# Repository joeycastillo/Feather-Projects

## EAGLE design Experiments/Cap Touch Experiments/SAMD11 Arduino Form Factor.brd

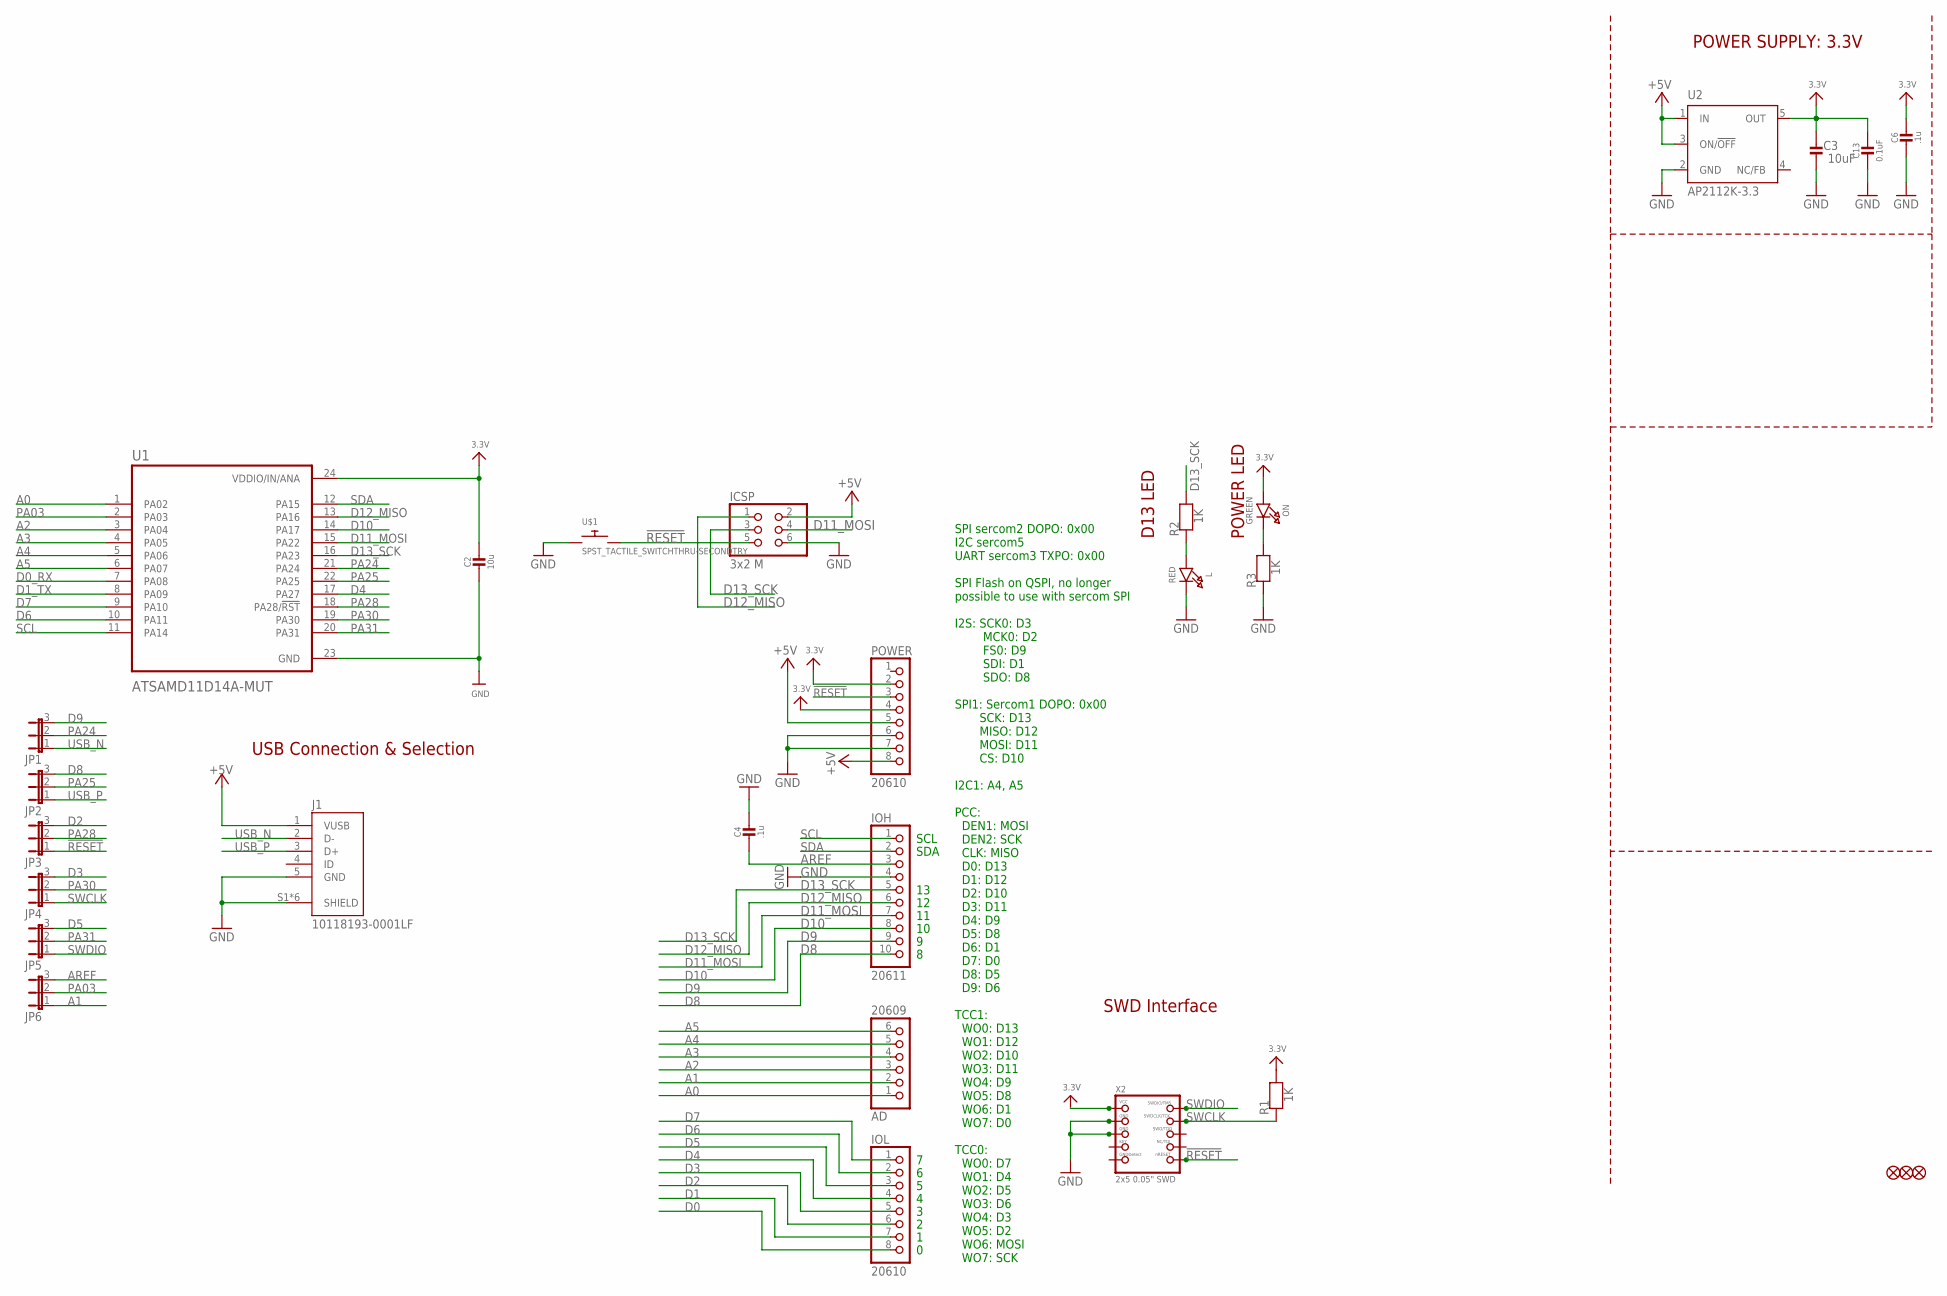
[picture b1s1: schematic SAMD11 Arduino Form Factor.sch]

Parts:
AD: 20609; 1X06_OVALWAVE
C2: 10u; 0805-NO
C3: 10uF; 0805-NO
C4, C6: .1u; 0805-NO
C13: 0.1uF; 0805-NO
FD1, FD2, FD3: FIDUCIAL_1MM
ICSP: 3x2 M; 2X03_ROUND_70MIL
IOH: 20611; 1X10_OVALWAVE
IOL: 20610; 1X08_OVALWAVE
J1: 10118193-0001LF; FCI_10118193-0001LF
JP1, JP2, JP3, JP4, JP5, JP6: JP2E; JP2
L: RED; CHIPLED_0805_NOOUTLINE
ON: GREEN; CHIPLED_0805_NOOUTLINE
POWER: 20610; 1X08_OVALWAVE
R1, R2, R3: 1K; 0805-NO
U1: ATSAMD11D14A-MUT; QFN50P400X400X90-25N
U2: AP2112K-3.3; SOT23-DBV
U$1: SPST_TACTILE_SWITCHTHRU-SECONDTRY; MJTP1250-TRY2
X2: 2x5 0.05" SWD; 2X05_1.27MM_BOX_POSTS

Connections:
3.3V: C2.2, C3.2, C6.2, C13.1, ON.A, POWER.2, POWER.4, R1.2, U1.24 (VDDIO/IN/ANA), U2.5 (OUT), X2.1 (VCC)
!RESET: ICSP.5, JP3.1, POWER.3, U$1.P$2, X2.10 (NRESET)
+5V: ICSP.2, POWER.5, POWER.8, U2.1 (IN), U2.3 (ON/!OFF)
A0: AD.1, U1.1 (PA02)
A1: AD.2, JP6.1
A2: AD.3, U1.3 (PA04)
A3: AD.4, U1.4 (PA05)
A4: AD.5, U1.5 (PA06)
A5: AD.6, U1.6 (PA07)
AREF: C4.1, IOH.3, JP6.3
D0: IOL.8
D0_RX: U1.7 (PA08)
D1: IOL.7
D1_TX: U1.8 (PA09)
D2: IOL.6, JP3.3
D3: IOL.5, JP4.3
D4: IOL.4, U1.17 (PA27)
D5: IOL.3, JP5.3
D6: IOL.2, U1.10 (PA11)
D7: IOL.1, U1.9 (PA10)
D8: IOH.10, JP2.3
D9: IOH.9, JP1.3
D10: IOH.8, U1.14 (PA17)
D11_MOSI: ICSP.4, IOH.7, U1.15 (PA22)
D12_MISO: ICSP.1, IOH.6, U1.13 (PA16)
D13_SCK: ICSP.3, IOH.5, R2.2, U1.16 (PA23)
GND: C2.1, C3.1, C4.2, C6.1, C13.2, ICSP.6, IOH.4, J1.5 (GND), J1.S1 (SHIELD), J1.S2 (SHIELD), J1.S3 (SHIELD), J1.S4 (SHIELD), J1.S5 (SHIELD), J1.S6 (SHIELD), L.C, POWER.6, POWER.7, R3.1, U1.23 (GND), U2.2 (GND), U$1.P$1, X2.3 (GND), X2.5 (GND)
unnamed: L.A, R2.1
unnamed: ON.C, R3.2
PA03: JP6.2, U1.2 (PA03)
PA24: JP1.2, U1.21 (PA24)
PA25: JP2.2, U1.22 (PA25)
PA28: JP3.2, U1.18 (PA28/!RST)
PA30: JP4.2, U1.19 (PA30)
PA31: JP5.2, U1.20 (PA31)
SCL: IOH.1, U1.11 (PA14)
SDA: IOH.2, U1.12 (PA15)
SWCLK: JP4.1, R1.1, X2.4 (SWDCLK)
SWDIO: JP5.1, X2.2 (SWDIO)
USB_N: J1.2 (D-), JP1.1
USB_P: J1.3 (D+), JP2.1

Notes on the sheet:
SDA
SCL
USB Connection & Selection
POWER SUPPLY: 3.3V
POWER LED
D13 LED
SWD Interface
SPI sercom2 DOPO: 0x00 I2C sercom5 UART sercom3 TXPO: 0x00 SPI Flash on QSPI, no longer possible to use with sercom SPI I2S: SCK0: D3 MCK0: D2 FS0: D9 SDI: D1 SDO: D8 SPI1: Sercom1 DOPO: 0x00 SCK: D13 MISO: D12 MOSI: D11 CS: D10 I2C1: A4, A5 PCC: DEN1: MOSI DEN2: SCK CLK: MISO D0: D13 D1: D12 D2: D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

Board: 2 copper layers, 31 parts (1 on the bottom side), 37 nets, no tracks yet.

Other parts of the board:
U$23: METROM4_REVF_TOP
U$27: METROM4_REVF_BOT

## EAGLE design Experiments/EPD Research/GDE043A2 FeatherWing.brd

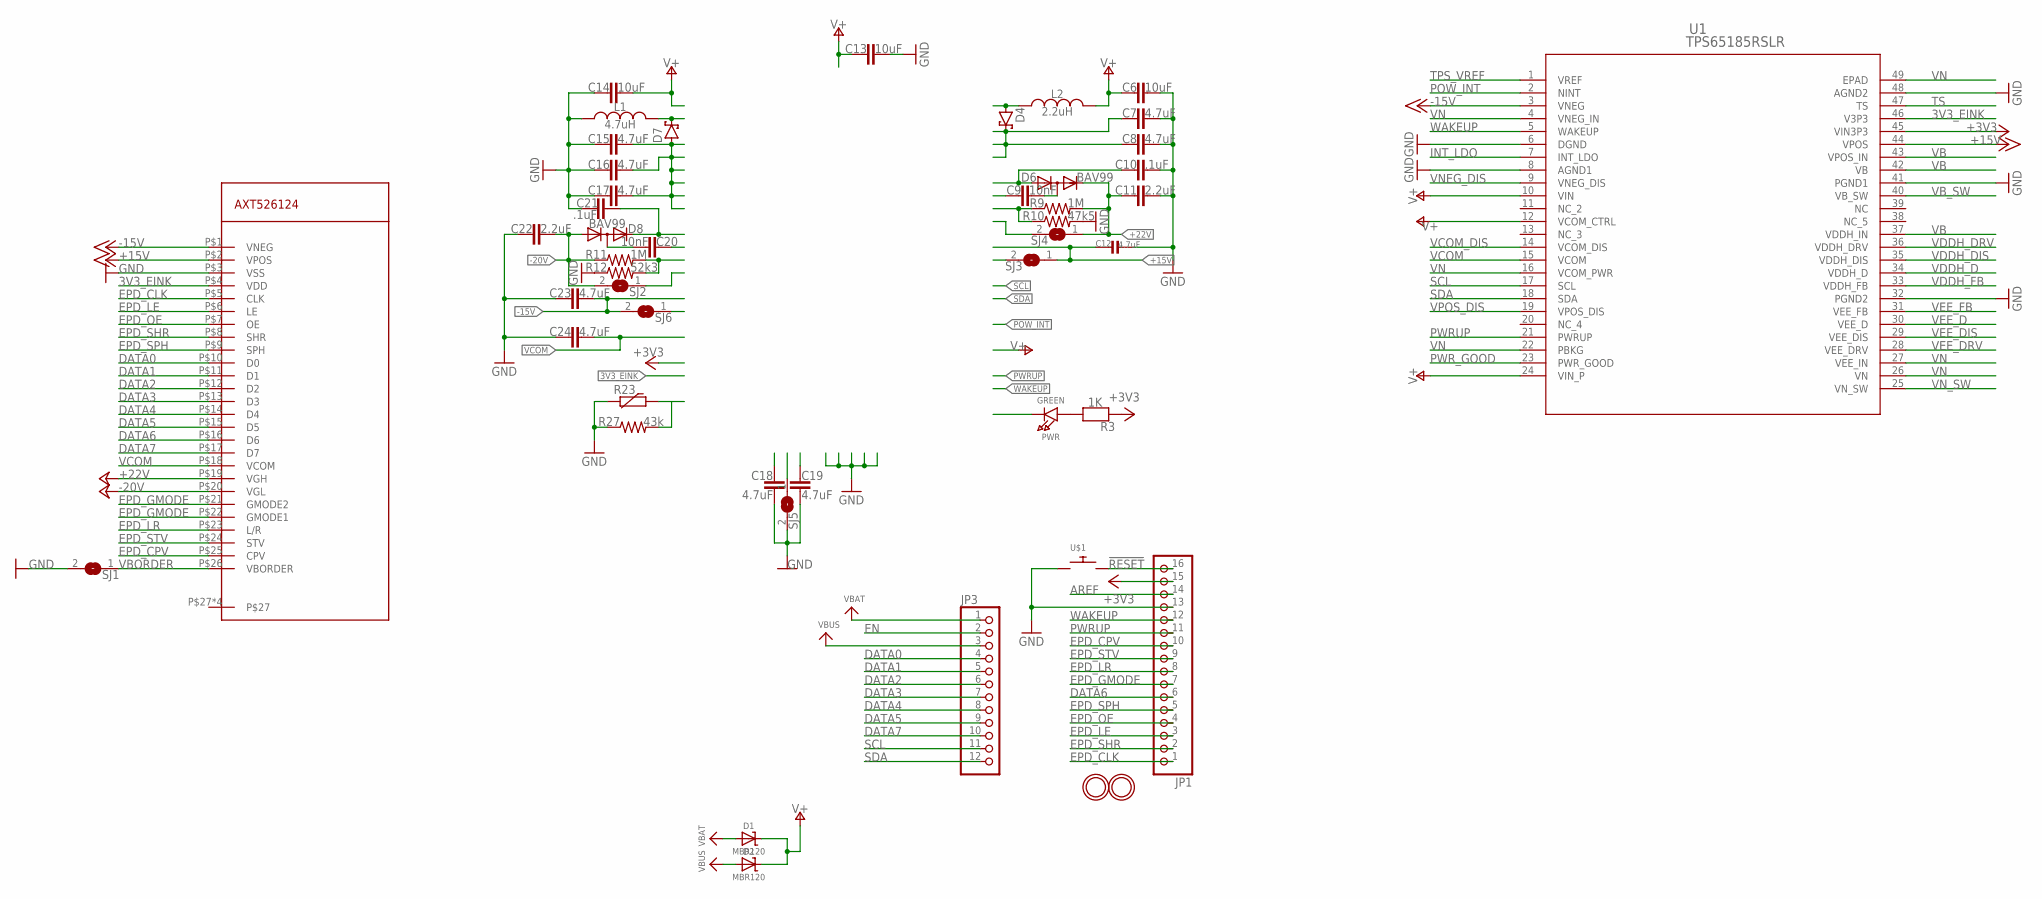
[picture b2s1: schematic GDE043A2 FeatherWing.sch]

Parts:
C6, C13, C14: 10uF; C0805K
C7, C8, C15, C16, C17, C18, C19, C23, C24: 4.7uF; C0805K
C9, C20: 10nF; C0805K
C10, C21: .1uF; C0805K
C11, C22: 2.2uF; C0805K
C12: 4.7uF; 0805_10MGAP
D1, D2: MBR120; SOD-123
D4, D7: MBR130T3G; SOD123
D6, D8: BAV99; SOT23
JP1: HEADER-1X16_MIN; 1X16_ROUND_MIN
JP3: HEADER-1X12_MIN; 1X12_ROUND_MIN
L1: 4.7uH; NR4012
L2: 2.2uH; NR4012
PWR: GREEN; CHIPLED_0805_NOOUTLINE
R3: 1K; 0805-NO
R9, R11: 1M; R0805
R10: 47k5; R0805
R12: 52k3; R0805
R23: R-EU_R0805; R0805
R27: 43k; R0805
SJ1, SJ2, SJ3, SJ4, SJ5, SJ6: SJ
U1: TPS65185RSLR; RSL48_4P4X4P4
U$1: SPST_TACTILE_SWITCHTHRU-SECONDTRY; MJTP1250-TRY2
U$2: AXT526124
U$31, U$32: MOUNTINGHOLE2.5; MOUNTINGHOLE_2.5_PLATED

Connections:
3V3_EINK: U1.46 (V3P3), U$2.P$4 (VDD)
!RESET: JP1.16, U$1.P$2
+3V3: JP1.15, R3.1, U1.45 (VIN3P3)
+15V: C12.2, SJ3.1, U1.44 (VPOS), U$2.P$2 (VPOS)
+22V: C11.1, D6.2 (C), R9.2, SJ4.1, U$2.P$19 (VGH)
-15V: C23.2, SJ6.2, U1.3 (VNEG), U$2.P$1 (VNEG)
-20V: C22.2, D8.1 (A), R11.1, SJ2.2, U$2.P$20 (VGL)
AREF: JP1.14
DATA0: JP3.4, U$2.P$10 (D0)
DATA1: JP3.5, U$2.P$11 (D1)
DATA2: JP3.6, U$2.P$12 (D2)
DATA3: JP3.7, U$2.P$13 (D3)
DATA4: JP3.8, U$2.P$14 (D4)
DATA5: JP3.9, U$2.P$15 (D5)
DATA6: JP1.6, U$2.P$16 (D6)
DATA7: JP3.10, U$2.P$17 (D7)
EN: JP3.2
EPD_CLK: JP1.1, U$2.P$5 (CLK)
EPD_CPV: JP1.10, U$2.P$25 (CPV)
EPD_GMODE: JP1.7, U$2.P$21 (GMODE2), U$2.P$22 (GMODE1)
EPD_LE: JP1.3, U$2.P$6 (LE)
EPD_LR: JP1.8, U$2.P$23 (L/R)
EPD_OE: JP1.4, U$2.P$7 (OE)
EPD_SHR: JP1.2, U$2.P$8 (SHR)
EPD_SPH: JP1.5, U$2.P$9 (SPH)
EPD_STV: JP1.9, U$2.P$24 (STV)
GND: C6.2, C7.2, C8.2, C10.2, C11.2, C12.1, C13.2, C14.1, C15.1, C16.1, C17.1, C18.1, C19.1, C21.1, C22.1, C23.1, C24.1, JP1.13, L1.P$1, R10.2, R12.1, R23.1, R27.1, SJ1.2, SJ5.2, U1.6 (DGND), U1.8 (AGND1), U1.32 (PGND2), U1.41 (PGND1), U1.48 (AGND2), U$1.P$1, U$2.P$3 (VSS)
INT_LDO: C18.2, U1.7 (INT_LDO)
unnamed: PWR.A, R3.2
unnamed: C9.2, D6.3 (AC)
unnamed: C20.2, D8.3 (AC)
POW_INT: U1.2 (NINT)
PWRUP: JP1.11, U1.21 (PWRUP)
PWR_GOOD: PWR.C, U1.23 (PWR_GOOD)
SCL: JP3.11, U1.17 (SCL)
SDA: JP3.12, U1.18 (SDA)
TPS_VREF: C19.2, U1.1 (VREF)
TS: R23.2, R27.2, U1.47 (TS)
V+: C6.1, C13.1, C14.2, D1.C, D2.C, L2.P$2, U1.10 (VIN), U1.12 (VCOM_CTRL), U1.24 (VIN_P)
VB: C7.1, C8.1, D4.1 (C), U1.37 (VDDH_IN), U1.42 (VB), U1.43 (VPOS_IN)
VBAT: D1.A, JP3.1
VBORDER: SJ1.1, U$2.P$26 (VBORDER)
VBUS: D2.A, JP3.3
VB_SW: D4.2 (A), L2.P$1, U1.40 (VB_SW)
VCOM: C24.2, U1.15 (VCOM), U$2.P$18 (VCOM)
VCOM_DIS: SJ5.1, U1.14 (VCOM_DIS)
VDDH_D: C10.1, D6.1 (A), U1.34 (VDDH_D)
VDDH_DIS: SJ4.2, U1.35 (VDDH_DIS)
VDDH_DRV: C9.1, U1.36 (VDDH_DRV)
VDDH_FB: R9.1, R10.1, U1.33 (VDDH_FB)
VEE_D: C21.2, D8.2 (C), U1.30 (VEE_D)
VEE_DIS: SJ2.1, U1.29 (VEE_DIS)
VEE_DRV: C20.1, U1.28 (VEE_DRV)
VEE_FB: R11.2, R12.2, U1.31 (VEE_FB)
VN: C15.2, C16.2, C17.2, D7.2 (A), U1.4 (VNEG_IN), U1.16 (VCOM_PWR), U1.22 (PBKG), U1.26 (VN), U1.27 (VEE_IN), U1.49 (EPAD)
VNEG_DIS: SJ6.1, U1.9 (VNEG_DIS)
VN_SW: D7.1 (C), L1.P$2, U1.25 (VN_SW)
VPOS_DIS: SJ3.2, U1.19 (VPOS_DIS)
WAKEUP: JP1.12, U1.5 (WAKEUP)

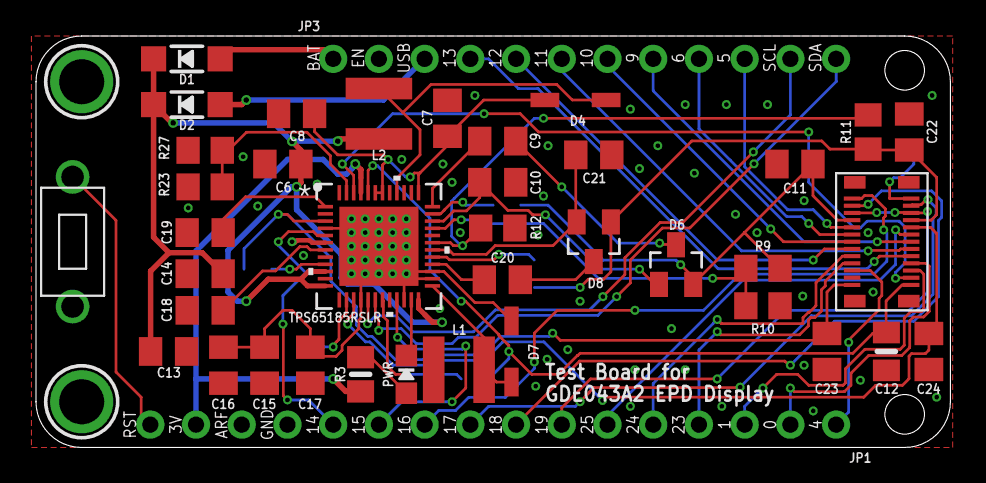
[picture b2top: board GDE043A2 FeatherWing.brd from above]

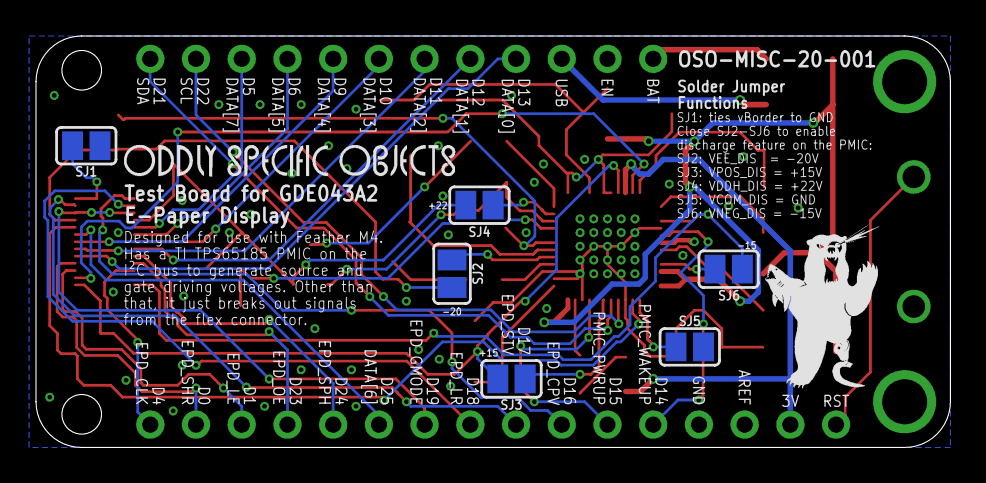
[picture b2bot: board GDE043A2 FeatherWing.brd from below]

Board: 2 copper layers, 50.8 x 22.9 mm, 50 parts (8 on the bottom side), 56 nets.

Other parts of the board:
U$4: OSO_WORDMARK_ONELINE_725MIL_1000DPI
U$7: OSO_BEAR_250X360MIL_1000DPI

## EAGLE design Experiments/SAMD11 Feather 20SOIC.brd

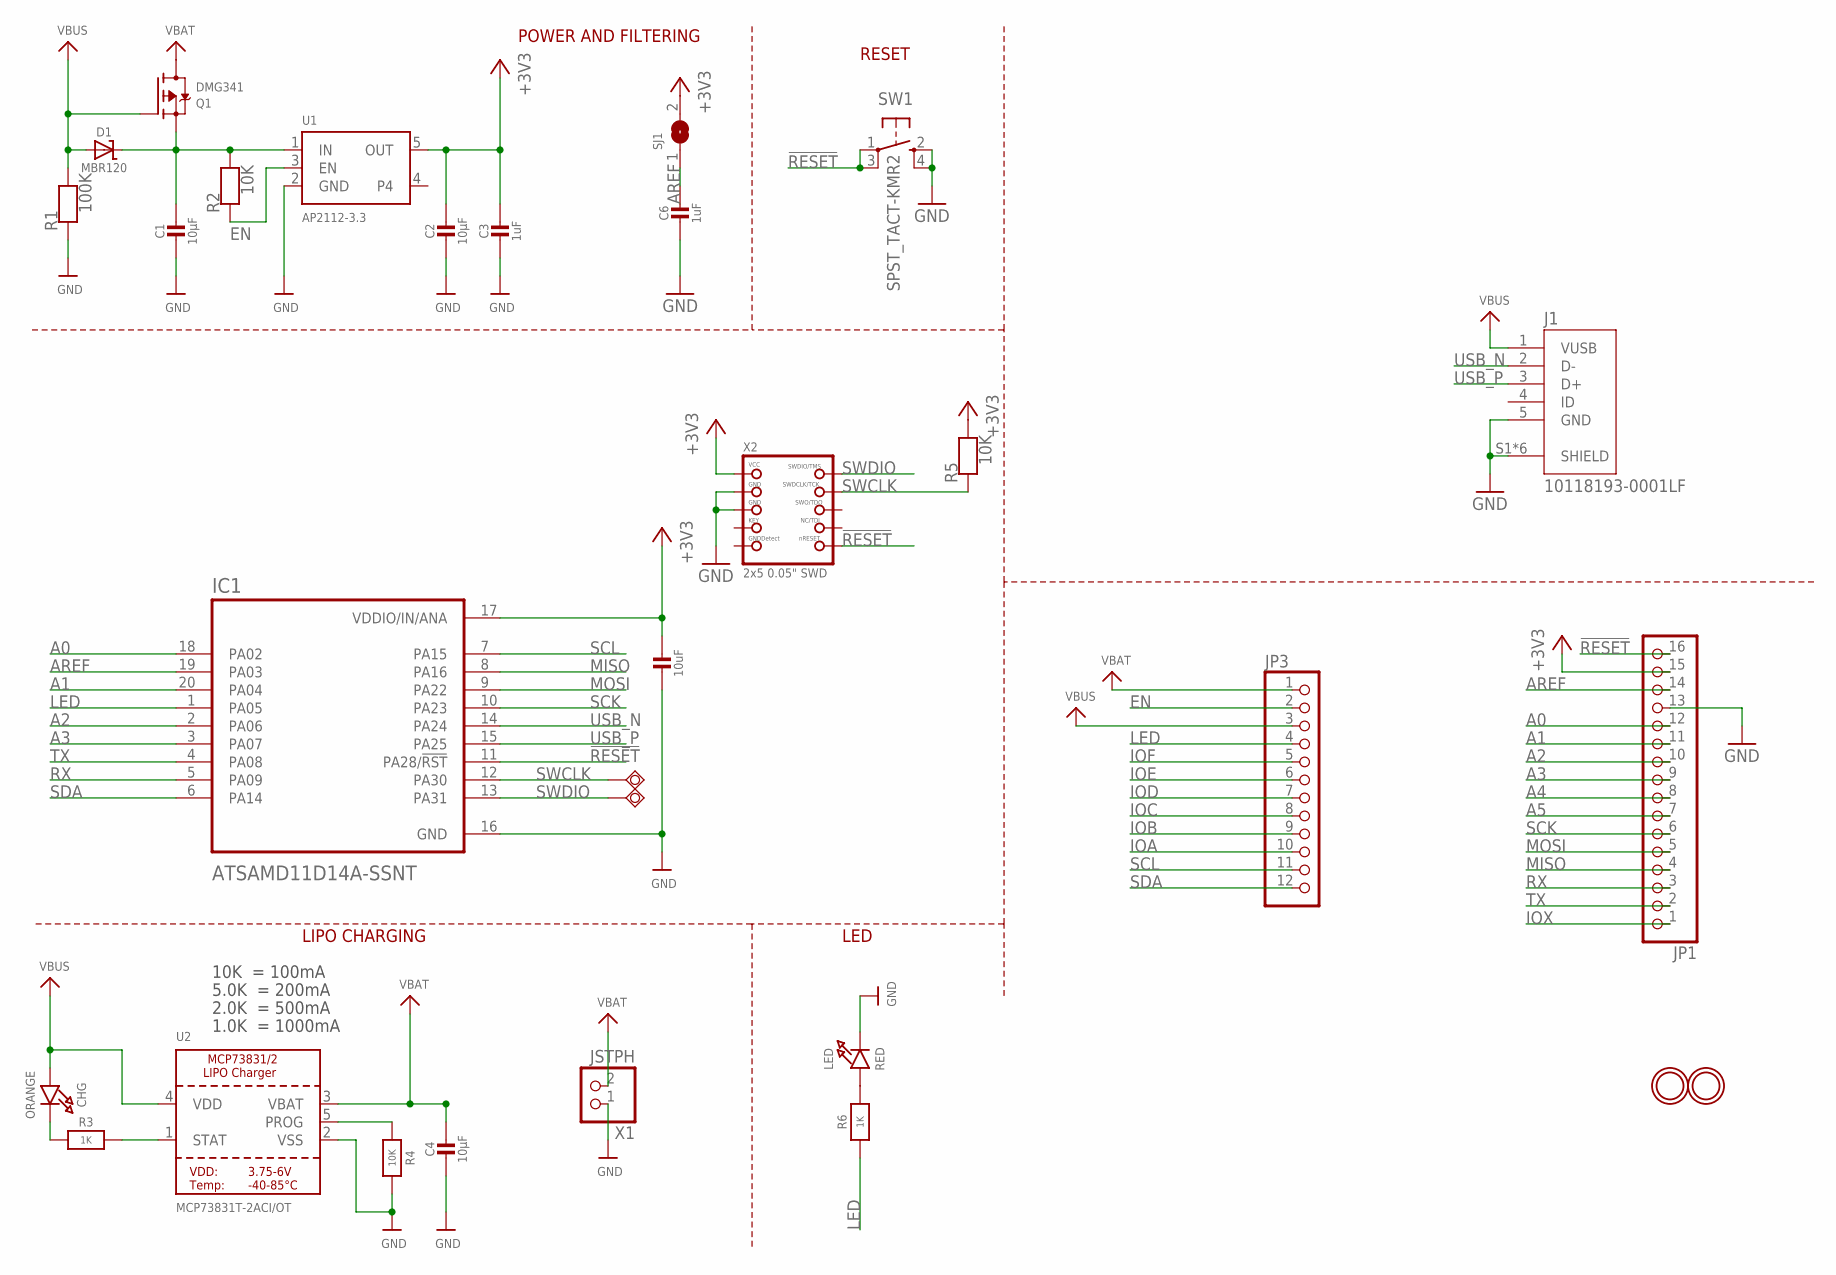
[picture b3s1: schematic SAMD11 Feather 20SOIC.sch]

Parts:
C1, C2, C4: 10µF; 0805-NO
C3, C6: 1uF; 0805-NO
C5: 10uF; 0805-NO
CHG: ORANGE; CHIPLED_0805_NOOUTLINE
D1: MBR120; SOD-123
IC1: ATSAMD11D14A-SSNT; SOIC127P1030X265-20N
J1: 10118193-0001LF; FCI_10118193-0001LF
JP1: HEADER-1X16_MIN; 1X16_ROUND_MIN
JP3: HEADER-1X12_MIN; 1X12_ROUND_MIN
LED: RED; CHIPLED_0805_NOOUTLINE
Q1: DMG341; SOT23-R
R1: 100K; 0805-NO
R2, R4, R5: 10K; 0805-NO
R3, R6: 1K; 0805-NO
SJ1: SOLDERJUMPERCLOSED; SOLDERJUMPER_CLOSEDWIRE
SW1: SPST_TACT-KMR2; KMR2
SWCLK: TPSQTP20R; TP20R
SWDIO: TPSQTP20R; TP20R
U1: AP2112-3.3; SOT23-5
U2: MCP73831T-2ACI/OT; SOT23-5
U$31, U$32: MOUNTINGHOLE2.5; MOUNTINGHOLE_2.5_PLATED
X1: JSTPH; JSTPH2
X2: 2x5 0.05" SWD; 2X05_1.27MM_BOX_POSTS

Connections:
!RESET: IC1.11 (PA28/!RST), JP1.16, SW1.1, SW1.3 (P1), X2.10 (NRESET)
+3V3: C2.1, C3.1, C5.1, IC1.17 (VDDIO/IN/ANA), JP1.15, R5.2, SJ1.2, U1.5 (OUT), X2.1 (VCC)
A0: IC1.18 (PA02), JP1.12
A1: IC1.20 (PA04), JP1.11
A2: IC1.2 (PA06), JP1.10
A3: IC1.3 (PA07), JP1.9
A4: JP1.8
A5: JP1.7
AREF: C6.1, IC1.19 (PA03), JP1.14, SJ1.1
CHG: CHG.C, R3.1
EN: JP3.2, R2.1, U1.3 (EN)
GND: C1.2, C2.2, C3.2, C4.2, C5.2, C6.2, IC1.16 (GND), J1.5 (GND), J1.S1 (SHIELD), J1.S2 (SHIELD), J1.S3 (SHIELD), J1.S4 (SHIELD), J1.S5 (SHIELD), J1.S6 (SHIELD), JP1.13, LED.C, R1.1, R4.2, SW1.2 (S), SW1.4 (S1), U1.2 (GND), U2.2 (VSS), X1.1, X2.3 (GND), X2.5 (GND)
IOA: JP3.10
IOB: JP3.9
IOC: JP3.8
IOD: JP3.7
IOE: JP3.6
IOF: JP3.5
IOX: JP1.1
LED: IC1.1 (PA05), JP3.4, R6.1
MISO: IC1.8 (PA16), JP1.4
MOSI: IC1.9 (PA22), JP1.5
unnamed: LED.A, R6.2
PROG: R4.1, U2.5 (PROG)
RX: IC1.5 (PA09), JP1.3
SCK: IC1.10 (PA23), JP1.6
SCL: IC1.7 (PA15), JP3.11
SDA: IC1.6 (PA14), JP3.12
STAT: R3.2, U2.1 (STAT)
SWCLK: IC1.12 (PA30), R5.1, SWCLK.TP, X2.4 (SWDCLK)
SWDIO: IC1.13 (PA31), SWDIO.TP, X2.2 (SWDIO)
TX: IC1.4 (PA08), JP1.2
USB_N: IC1.14 (PA24), J1.2 (D-)
USB_P: IC1.15 (PA25), J1.3 (D+)
VBAT: C4.1, JP3.1, Q1.3 (D), U2.3 (VBAT), X1.2
VBUS: CHG.A, D1.A, J1.1 (VUSB), JP3.3, Q1.1 (G), R1.2, U2.4 (VDD)
VHI: C1.1, D1.C, Q1.2 (S), R2.2, U1.1 (IN)

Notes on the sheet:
LIPO CHARGING
LED
RESET
POWER AND FILTERING
10K = 100mA
5.0K = 200mA
2.0K = 500mA
1.0K = 1000mA

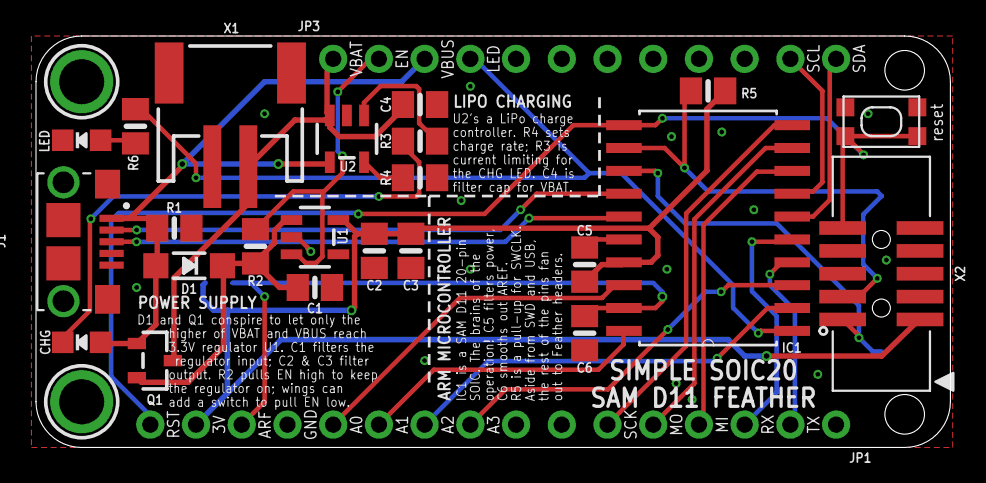
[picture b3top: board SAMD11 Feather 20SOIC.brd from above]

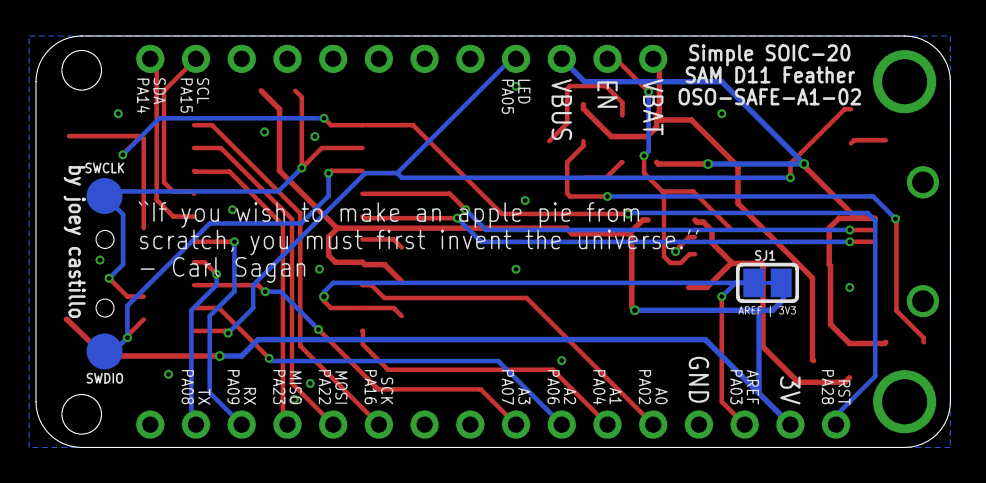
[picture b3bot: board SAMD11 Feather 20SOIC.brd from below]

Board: 2 copper layers, 50.8 x 22.9 mm, 30 parts (3 on the bottom side), 28 nets.

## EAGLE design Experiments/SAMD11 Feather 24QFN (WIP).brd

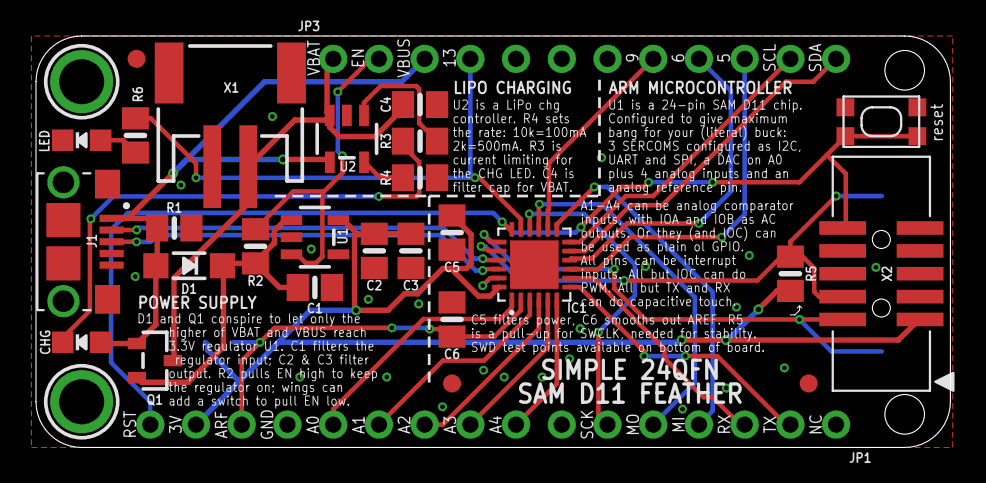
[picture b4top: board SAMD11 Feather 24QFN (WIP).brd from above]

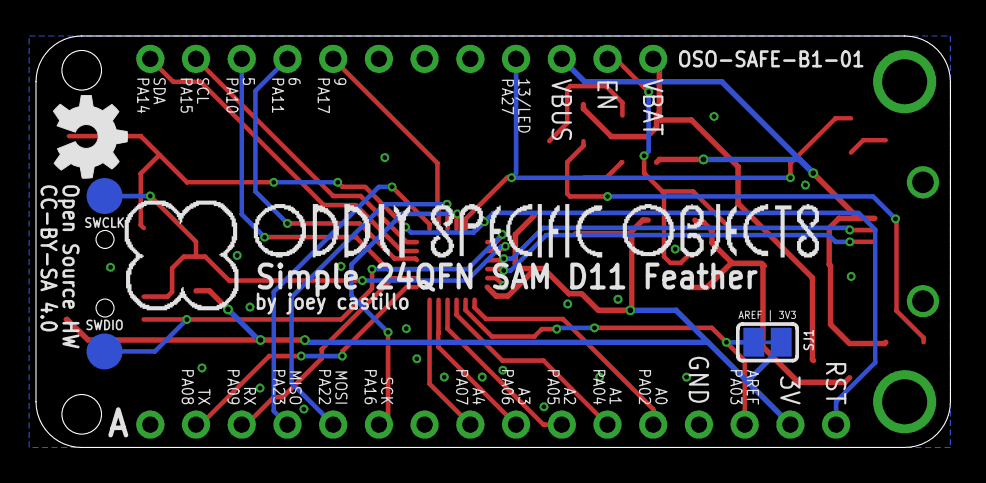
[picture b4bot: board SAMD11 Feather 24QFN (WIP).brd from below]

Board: 2 copper layers, 50.8 x 22.9 mm, 37 parts (7 on the bottom side), 32 nets.

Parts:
C1, C2, C4: 10µF; 0805-NO
C3, C6: 1uF; 0805-NO
C5: 10uF; 0805-NO
CHG: ORANGE; CHIPLED_0805_NOOUTLINE
D1: MBR120; SOD-123
FID1, FID3, FID4: FIDUCIAL_1MM
GOLD_ORB_SM1: OSHWLOGOLOGO5MM; OSHW_5MM
IC1: ATSAMD11D14A-MUT; QFN50P400X400X90-25N
J1: 10118193-0001LF; FCI_10118193-0001LF
JP1: 1X16_ROUND_MIN
JP3: 1X12_ROUND_MIN
LED: RED; CHIPLED_0805_NOOUTLINE
Q1: DMG341; SOT23-R
R1: 100K; 0805-NO
R2, R4, R5: 10K; 0805-NO
R3, R6: 1K; 0805-NO
SJ1: SOLDERJUMPER_CLOSEDWIRE
SW1: SPST_TACT-KMR2; KMR2
SWCLK: TPSQTP20R; TP20R
SWDIO: TPSQTP20R; TP20R
U1: AP2112-3.3; SOT23-5
U2: MCP73831T-2ACI/OT; SOT23-5
U$2: OSO_BEAR; OSO_BEAR_750MIL
U$3: OSO_GRAPHIC
U$5: OSO_TEXTOSO_TEXT_ONELINE_125MIL; OSO_ONELINE_125MIL
U$31, U$32: MOUNTINGHOLE2.5; MOUNTINGHOLE_2.5_PLATED
X1: JSTPH; JSTPH2
X2: 2x5 0.05" SWD; 2X05_1.27MM_BOX_POSTS

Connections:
!RESET: IC1.18, JP1.16, SW1.1, SW1.3, X2.10
+3V3: C2.1, C3.1, C5.1, IC1.24, JP1.15, R5.2, SJ1.2, U1.5, X2.1
A0: IC1.1, JP1.12
A1: IC1.3, JP1.11
A2: IC1.4, JP1.10
A3: IC1.5, JP1.9
A4: IC1.6, JP1.8
AREF: C6.1, IC1.2, JP1.14, SJ1.1
CHG: CHG.C, R3.1
EN: JP3.2, R2.1, U1.3
GND: C1.2, C2.2, C3.2, C4.2, C5.2, C6.2, IC1.23, J1.5, J1.S1, J1.S2, J1.S3, J1.S4, J1.S5, J1.S6, JP1.13, LED.C, R1.1, R4.2, SW1.2, SW1.4, U1.2, U2.2, X1.1, X2.3, X2.5
IOA: IC1.9, JP3.10
IOB: IC1.10, JP3.9
IOC: IC1.14, JP3.8
LED: IC1.17, JP3.4, R6.1
MISO: IC1.13, JP1.4
MOSI: IC1.15, JP1.5
unnamed: LED.A, R6.2
PROG: R4.1, U2.5
RX: IC1.8, JP1.3
SCK: IC1.16, JP1.6
SCL: IC1.12, JP3.11
SDA: IC1.11, JP3.12
STAT: R3.2, U2.1
SWCLK: IC1.20, R5.1, SWCLK.TP, X2.4
SWDIO: IC1.19, SWDIO.TP, X2.2
TX: IC1.7, JP1.2
USB_N: IC1.21, J1.2
USB_P: IC1.22, J1.3
VBAT: C4.1, JP3.1, Q1.3, U2.3, X1.2
VBUS: CHG.A, D1.A, J1.1, JP3.3, Q1.1, R1.2, U2.4
VHI: C1.1, D1.C, Q1.2, R2.2, U1.1

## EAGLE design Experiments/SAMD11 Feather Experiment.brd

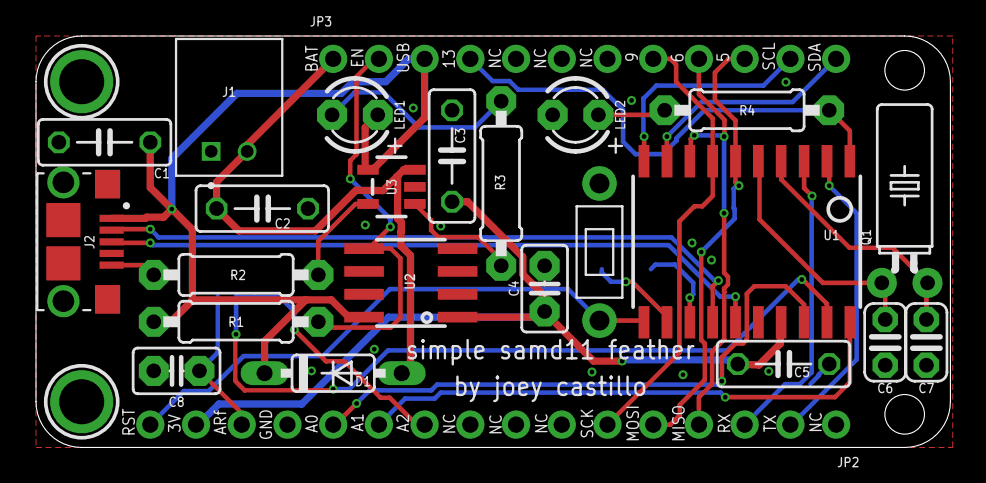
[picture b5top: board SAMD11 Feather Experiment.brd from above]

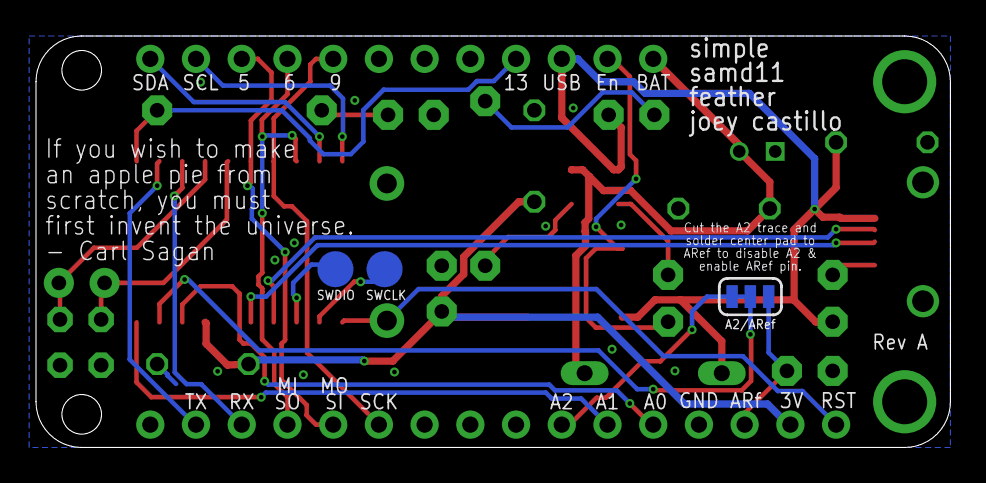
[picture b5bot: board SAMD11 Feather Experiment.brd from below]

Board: 2 copper layers, 50.8 x 22.9 mm, 29 parts (3 on the bottom side), 29 nets.

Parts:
C1, C2, C3, C5: 10uF; C050-025X075
C4, C8: 1uF; C025-025X050
C6, C7: 22pf; C025-024X044
D1: SCHOTTKY; DO35-7
J1: S2B-PH-K-S(LF)(SN); JST_S2B-PH-K-S(LF)(SN)
J2: 10118193-0001LF; FCI_10118193-0001LF
JP1: A2/VREF; SMT-JUMPER_3_1-NC_TRACE_SILK
JP2: 1X16_ROUND_MIN
JP3: 1X12_ROUND_MIN
LED1: ORANGE; LED3MM
LED2: RED; LED3MM
Q1: 32.768; TC38H
R1: 100k; 0207/9
R2: 4.7K; 0207/9
R3, R4: 1K; 0207/9
SW1: MJTP1250_SPST_SWITCH; MJTP1250
SWCLK: TPSQTP20R; TP20R
SWDIO: TPSQTP20R; TP20R
U1: ATSAMD11D14A; SOIC20L
U2: MICROBUILDER_SOIC8_150MIL
U3: MCP73831T-2ACI/OT; SOT23-5
U$31, U$32: MOUNTINGHOLE2.5; MOUNTINGHOLE_2.5_PLATED

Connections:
!RESET: JP2.16, SW1.P$1, U1.11
+3V3: C3.1, C4.1, C5.1, JP2.15, U1.17, U2.1
A0: JP2.12, U1.18
A1: JP2.11, U1.20
A2: JP1.3, JP2.10
A2/VREF: JP1.2, U1.19
EN: JP3.2, R1.1, U2.5
GND: C1.2, C2.2, C3.2, C4.2, C5.2, C6.2, C7.2, C8.2, J1.1, J2.5, JP2.13, LED2.K, R2.1, SW1.P$2, U1.16, U2.6, U2.7, U3.2
LED/13: JP3.4, R4.1, U1.1
MISO/6: JP2.4, JP3.9, U1.8
MOSI/5: JP2.5, JP3.10, U1.6
unnamed: LED1.K, R3.2
unnamed: LED2.A, R4.2
PROG: R2.2, U3.5
RX: JP2.3, U1.3
SCK/9: JP2.6, JP3.8, U1.7
SCL: JP3.11, U1.10
SDA: JP3.12, U1.9
STAT: R3.1, U3.1
SWCLK: SWCLK.TP, U1.12
SWDIO: SWDIO.TP, U1.13
TX: JP2.2, U1.2
USB/DM: J2.2, U1.14
USB/DP: J2.3, U1.15
VBAT: C2.1, D1.A, J1.2, JP3.1, U3.3
VBUS: C1.1, D1.C, J2.1, JP3.3, LED1.A, R1.2, U2.8, U3.4
VREF: C8.1, JP1.1, JP2.14
XIN: C7.1, Q1.2, U1.4
XOUT: C6.1, Q1.1, U1.5

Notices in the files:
Experiments/SAMD11 Feather 24QFN (WIP).brd:
CC-BY-SA 4.0
Experiments/Tiny Book/OSO-TIBO-A1-01.brd:
CC-BY Acknowledgments:
So many footprints and
parts and their libraries:
microbuilder: This work is placed in the public domain, and may be freely used for commercial and non-commercial work with the following conditions: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
SparkFun-Jumpers: Licensing: Creative Commons ShareAlike 4.0 International - https://creativecommons.org/licenses/by-sa/4.0
